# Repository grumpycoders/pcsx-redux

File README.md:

<a href='https://ko-fi.com/nicolasnoble' target='_blank'>Buy Me a Coffee at ko-fi.com</a>

|Platform|Build status|Download|
|--------|------------|--------|
|Windows x64 build||[Windows Intel 64-bits](https://distrib.app/pub/org/pcsx-redux/project/dev-win-x64)|
|Linux x64 build||[Linux Intel 64-bits (AppImage)](https://distrib.app/pub/org/pcsx-redux/project/dev-linux-x64)|
|Linux arm64 build||[Linux Arm 64-bits (AppImage)](https://distrib.app/pub/org/pcsx-redux/project/dev-linux-arm64)|
|macOS build||[macOS Arm](https://distrib.app/pub/org/pcsx-redux/project/dev-macos-arm)|
|Browser build||[Run in the browser (experimental)](https://tools.psx.dev/redux/)|

To discuss this emulator specifically, please join our Discord server:

To discuss PlayStation 1 development, hacking, and reverse engineering in general, please join the PSX.Dev Discord server:

# PCSX-Redux

## What?
The PCSX-Redux project is a collection of tools, research, hardware design, and libraries aiming at development and reverse engineering on the PlayStation 1. The core product itself, PCSX-Redux, is yet another fork of the Playstation emulator, PCSX. While the work here is very much in progress, the goal is roughly the following:

 - Bring the codebase to more up to date code standards.
 - Get rid of the plugin system and create a single monolithic codebase that handles all aspects of the playstation emulation.
 - Write everything on top of OpenGL3+/ImGui for portability and readability.
 - Improve the debugging experience.
 - Improve the rendering experience.

Please consult [the documentation pages](https://pcsx-redux.consoledev.net) for more information on the emulator itself.

The [tools](tools) directory contains a few tools that can be used to work with PlayStation 1 software. The [wiki](https://github.com/pcsx-redux/pcsx-redux/wiki) directory contains a few research information that are not directly related to the emulator itself. The [mips](src/mips) directory contains various pieces of code targeting the PlayStation 1, and importantly, the OpenBIOS project, which is a MIPS R3000A BIOS implementation that can be used to boot PlayStation 1 games without the need for a retail BIOS. And the [hardware](hardware) directory contains various hardware designs that can be used with the PlayStation 1.

## Where?
|Download page|
|--------|
|[Windows Intel 64-bits](https://distrib.app/pub/org/pcsx-redux/project/dev-win-x64)|
|[Windows Intel 64-bits CLI](https://distrib.app/pub/org/pcsx-redux/project/dev-win-cli-x64)|
|[Linux Intel 64-bits (AppImage)](https://distrib.app/pub/org/pcsx-redux/project/dev-linux-x64)|
|[Linux Arm 64-bits (AppImage)](https://distrib.app/pub/org/pcsx-redux/project/dev-linux-arm64)|
|[MacOS Arm](https://distrib.app/pub/org/pcsx-redux/project/dev-macos-arm)|
|[Browser (WebAssembly, experimental)](https://tools.psx.dev/redux/)|

All native builds are 64-bit only, and need a GPU and driver that can create at least an OpenGL 3.0 context. The emulator asks for a 3.3 core profile first and falls back to 3.0 if that fails.

The browser build is highly experimental and not really functional yet: expect missing features and breakage. It is redeployed from each push to main whose wasm build succeeds. It runs the CPU interpreter only and boots OpenBIOS, and it needs WebGL2 and SharedArrayBuffer. The first visit reloads the page once to enable SharedArrayBuffer.

The Linux AppImages are built on Ubuntu 24.04 and need a distribution at least that recent. On older ones, the Windows build runs under Wine 11: replace `pcsx-redux.exe`, the launcher that checks for the Visual C++ runtime, with `pcsx-redux.main` renamed to `pcsx-redux.exe`.

### Note:
The macOS version of PCSX-Redux is not currently signed with a developer certificate so you may see a security warning when opening the application.

If you see a dialog with the message:

> “PCSX-Redux” can’t be opened because Apple cannot check it for malicious software.

You can allow the application to run by doing either of the following. You only need to do this once for freshly downloaded copies of PCSX-Redux.

- Right-click the app and select Open. This signals an explicit decision on your part that you really want to open it, and adds a new "Open" button to the security warning dialog.

- Alternatively, go to macOS Settings > Privacy & Security. Scroll down to see a section that will let you allow the app.

## How?
The code is meant to be built using very modern compilers. Also it's still fairly experimental, and lots of things can break. If you still want to proceed, here are instructions to build it on Linux, MacOS and Windows. The code now comes in two big parts: the emulator itself, and [OpenBIOS](https://github.com/pcsx-redux/nugget/tree/main/openbios), which can be used as an alternative to the retail, copyright protected BIOS.

### Getting sources
The only location for the source is [on GitHub](https://github.com/pcsx-redux/pcsx-redux/).
Clone recursively, as the project uses submodules:
```
git clone --recursive https://github.com/pcsx-redux/pcsx-redux.git
```

### Windows
Install [Visual Studio 2022 Community Edition](https://visualstudio.microsoft.com/thank-you-downloading-visual-studio/?sku=Community&rel=16) using the `Desktop development with C++` workload. Open the file `vsprojects\pcsx-redux.sln`, select `pcsx-redux -> pcsx-redux`, right click, `Set as Startup Project`, and hit `F7` to build. The project follows the open-and-build paradigm with no extra step, so no specific dependency ought to be needed, as [NuGet](https://www.nuget.org/) will take care of downloading them automatically for you on the first build.

Note: If you get an error saying `hresult e_fail has been returned from a call to a com component`, you might need to delete the .suo file in vsproject/vs, restart Visual Studio and retry.

If you want to compile OpenBIOS or other PS1 software, you need to install a MIPS toolchain on Windows. You can do this by copy-pasting the following into a command prompt:

```powershell
powershell -c "& { iwr -UseBasicParsing https://bit.ly/mips-ps1 | iex }"
```

Then, open a new command prompt, and type the following:

```
mips install 16.2.0
```

To manually install this script, you can download it from [here](https://bit.ly/mips-ps1), and then install it with the following command:

```powershell
powershell -ExecutionPolicy Unrestricted -File mips.ps1 self-install C:\path\to\destination
```

You can leave the installation path blank to install the script in the Application Data folder.

Once the toolchain is installed, you can compile OpenBIOS using `make -C src/mips/openbios`.

### Linux
Run `./dockermake.sh appimage`. You need [docker](https://en.wikipedia.org/wiki/Docker_(software)) for this to work. This will create an [AppImage](https://appimage.org/) file, called `PCSX-Redux-HEAD-x86_64.AppImage` or `PCSX-Redux-HEAD-aarch64.AppImage` depending on your machine, which a self-hosted binary containing all of its required dependencies. Alternatively, if you do not want to use Docker, you can also simply install the dependencies listed below and run `make`.

#### GNU/Linux Dependencies

If you're only interested in compiling psx code, you can simply clone the pcsx-redux repo, then build the mips toolchain with [this script](https://github.com/pcsx-redux/pcsx-redux/blob/main/tools/linux-mips/spawn-compiler.sh), then follow the instructions in `/pcsx-redux/src/mips/psyq/README.md` to convert the PsyQ libraries. You might find them pre-compiled online.

 - Debian derivatives ( for full emulator compilation ):

```bash
sudo apt-get install -y build-essential git make pkg-config clang g++ libcapstone-dev libfreetype-dev libavcodec-dev libavformat-dev libavutil-dev libcurl4-openssl-dev libsdl3-dev libswresample-dev libuv1-dev zlib1g-dev
```

The mips toolchain isn't packaged by Debian or Ubuntu, so build it from source:

```bash
sudo apt-get install -y wget bzip2 xz-utils bison flex texinfo libgmp-dev libmpfr-dev libmpc-dev
sudo bash tools/linux-mips/spawn-compiler.sh
```

 - Arch derivatives :

The `pcsx-redux-git` package can be installed from the AUR using your AUR helper of choice (e.g., paru):

```bash
paru -S pcsx-redux-git
```

Alternatively, the following steps describe how to install dependencies and compile manually:

```bash
sudo pacman -S --needed capstone clang git make pkg-config ffmpeg libuv zlib sdl3 curl xorg-server-xvfb imagemagick
```
The mipsel environment can be installed from [AUR](https://wiki.archlinux.org/index.php/Aur) : [mipsel-none-elf-binutils](https://aur.archlinux.org/packages/mipsel-none-elf-binutils/) and [mipsel-none-elf-gcc](https://aur.archlinux.org/packages/mipsel-none-elf-gcc/) using your [AURhelper](https://wiki.archlinux.org/index.php/AUR_helpers) of choice:

```bash
trizen -S mipsel-none-elf-binutils mipsel-none-elf-gcc
```
You can then just enter the 'pcsx-redux' directory and compile without using docker with `make`.

Building OpenBIOS on Linux can be done with `./dockermake.sh -C src/mips/openbios`, or with `make -C src/mips/openbios` once you have a mipsel-none-elf toolchain. If you have a different mips compiler, you'll need to override some variables, such as `PREFIX` and `FORMAT`.

### MacOS
You need MacOS Catalina or later with the latest XCode to build, as well as a few [homebrew](https://brew.sh/) packages. Run the [brew installation script](https://github.com/pcsx-redux/pcsx-redux/blob/main/.github/scripts/install-brew-dependencies.sh) to get all the necessary dependencies. Simply run `make` to build.

Compiling OpenBIOS will require a mips compiler, which you can install from our [Homebrew tap](https://github.com/pcsx-redux/homebrew-mips):
```bash
brew install pcsx-redux/mips/mipsel-none-elf-gcc
```

Then, you can compile OpenBIOS using `make -C ./src/mips/openbios`.

## Who?
I used to contribute to the PCSX codebase. It is very likely that a sourceforge account of mine still has write access to the old cvs repository for PCSX. A long time ago, I contributed the telnet debugger, and the parallel port support. This means I am fairly familiar with this codebase, and I am also ashamed of the contributions I have done 15+ years ago, as one should.

Since the inception of this codebase, several people have contributed to it. Please refer to the [AUTHORS](AUTHORS) file for a (hopefully) exhaustive list.

## Why?
When Sony released the Playstation Classic recently, I came to realize two things: first, the state of the Playstation emulation isn't that great, and second, the only half-decent debugging tool still available for this console is that old telnet debugger I wrote eons ago, while other emulators out there for other consoles gained a lot of debugging superpowers. I think it was time for the Playstation emulation to get to better standards with regards to debuggability. I also felt I had a responsability to cleaning up some of the horrors I've introduced myself in the codebase long ago, and that made me cry a little looking at them. Hopefully, I got better at programming. Hopefully.

## Status?
The codebase still requires a lot of cleanup, and while the product is usable in its current state and lots can be achieved with it, there is still ways to go for reaching the first stable release. If you want to help with localization, you can find the translation project [on transifex](https://explore.transifex.com/grumpycoders/pcsx-redux/).

### What works?
- Dynamic Recompiler (x86-64, experimental arm64 support)
- interpreted CPU
- software GPU
- OpenGL GPU (highly experimental, still in active development)
- support for visual enhancements:
  - Linear and nearest neighbour filtering (Software and OpenGL renderer)
  - Rendering in true colour (Results in better colours, OpenGL renderer only)
  - Antialiasing (Implemented via MSAA, OpenGL renderer only)
  - Ability to optionally render polygons as wireframe or as vertices (Helps with debugging, OpenGL renderer only)
  - Hopefully more to come in the feature, such as upscaling, integer scaling, PGXP, and more
- VRAM viewer and debugger
- fully featured MIPS debugger
- memory cards
- memory card manager
- XBox controller support
- digital and analog controller emulation, Playstation Mouse emulation
- Lua scripting
- SPU debugger
- in-app shader editor and built-in crt-lottes shader
- customizable UI
- save states

### What still requires some work?
- fix remaining OpenGL renderer bugs (No mask bit emulation, missing commands, etc) and add more graphics enhancements
- proper SPU multithreaded code
- better customization
- more generic dynarec
- hook more emulator functions to Lua
- see [TODO](TODO.md) for more

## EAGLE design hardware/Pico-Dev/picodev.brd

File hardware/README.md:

# Hardware

This directory contains various hardware mods and addons for the PlayStation 1. The PCBs have been designed using Eagle, and pre-rendered gerber files are provided. When applicable, [jlcpcb](https://jlcpcb.com) build files are provided (BoM and assembly CSV files).

Some of these designs have been thoroughly documented [in the wiki](https://github.com/grumpycoders/pcsx-redux/wiki).

* [MC-Breakout](MC-Breakout) - A breakout board for the PlayStation 1's memory card slot. This board is made to fit directly into the slot without a case, and provides a simple header to connect to the memory card slot's signals.

* [PIO-Breakout](PIO-Breakout) - A breakout board for the PlayStation 1's parallel I/O port. This board is designed to function as a pass-through, which can then be used to sniff the parallel I/O port's signals when connecting another flash cart to it.

* [PIO-Dev](PIO-Dev) - A development board for the PlayStation 1's parallel I/O port. The board has [extensive documentation](https://github.com/grumpycoders/pcsx-redux/wiki/PIODev-Board) on the wiki.

* [PIO-Dev-Lite](PIO-Dev-Lite) - A smaller version of the PIO-Dev board, with a few less features. It is fitted with a writable flash, an FT232H chip for fast communication, and header pins to connect a [CH376 module](https://www.google.com/search?q=ch376+module). The CH376 module can be used with [Skitchin's project](https://github.com/johnbaumann/psx-wch376s) to access USB mass storage.

* [Pico-Dev](Pico-Dev) - A development board for the PlayStation 1 based on the Raspberry Pi Pico. It is extremely simple to manufacture, as its BoM is exactly one [RP2040-Zero](https://www.waveshare.com/rp2040-zero.htm), one PIO port, and one Schottky diode. The firmware for it is avaiable at [https://github.com/johnbaumann/PicoDev](https://github.com/johnbaumann/PicoDev).

* [PowerReplayUSB](PowerReplayUSB) - An easy to build mod for the popular and readily available [Power Replay Flash Cart](https://www.aliexpress.com/w/wholesale-ps1-power-replay.html) which adds USB support to it. The USB support is provided by the [FT232H](https://ftdichip.com/products/ft232hq/) chip, and [unirom](https://unirom.github.io/) has support for it. There is a [USB-C alternative](PowerReplayUSBC) available as well.

The projects featuring FT232H chips can be used for ultra fast communication between the PlayStation 1 and a computer. [Tools made by danhans42](https://github.com/danhans42/psx232h) can be used for this.

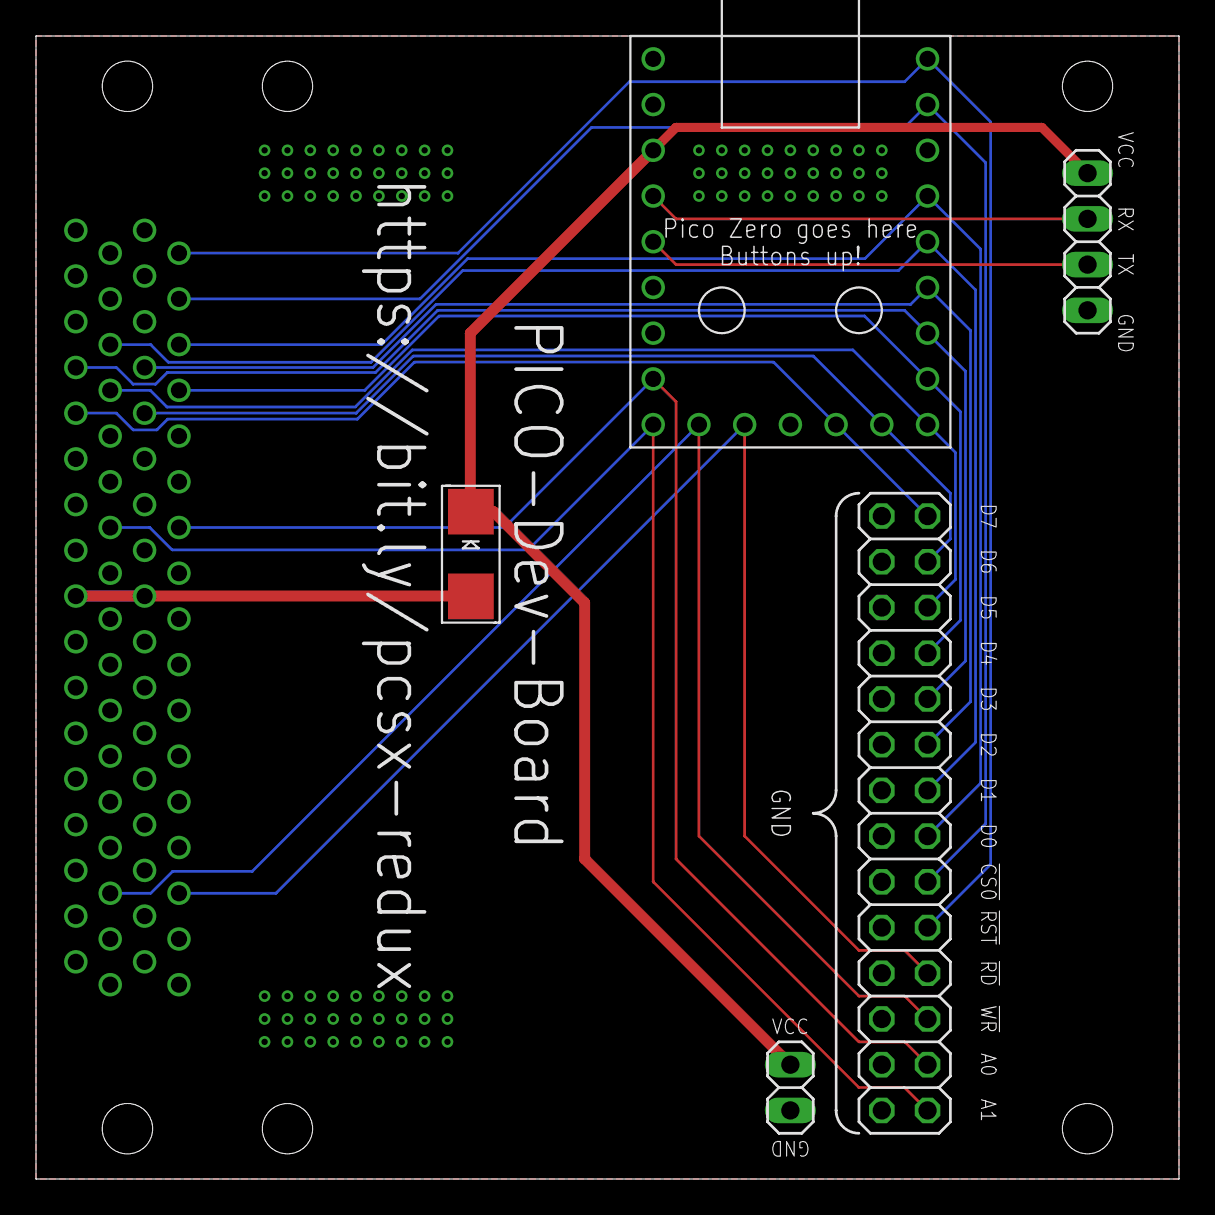
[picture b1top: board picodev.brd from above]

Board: 2 copper layers, 63.5 x 63.5 mm, 6 parts (1 on the bottom side), 19 nets.

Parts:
D: SCHOTTKYSMA; SMADIODE
DEBUG: 2X14
PIO: PIOCONNPIOCONN-S; PIOCONN
PWR: 1X02
U$1: PICO-ZERO
UART: 1X04

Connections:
!CS0: DEBUG.18, PIO.4, U$1.2
!RD: DEBUG.22, PIO.30, U$1.13
!RESET: DEBUG.20, PIO.2, U$1.1
!WR: DEBUG.24, PIO.64, U$1.14
A0: DEBUG.26, PIO.14, U$1.16
A1: DEBUG.28, PIO.48, U$1.15
D0: DEBUG.16, PIO.6, U$1.4
D1: DEBUG.14, PIO.40, U$1.5
D2: DEBUG.12, PIO.7, U$1.6
D3: DEBUG.10, PIO.41, U$1.7
D4: DEBUG.8, PIO.8, U$1.8
D5: DEBUG.6, PIO.42, U$1.9
D6: DEBUG.4, PIO.9, U$1.10
D7: DEBUG.2, PIO.43, U$1.11
GND: DEBUG.1, DEBUG.3, DEBUG.5, DEBUG.7, DEBUG.9, DEBUG.11, DEBUG.13, DEBUG.15, DEBUG.17, DEBUG.19, DEBUG.21, DEBUG.23, DEBUG.25, DEBUG.27, PIO.1, PIO.16, PIO.19, PIO.34, PIO.35, PIO.50, PIO.53, PIO.68, PWR.1, U$1.22, UART.1
PIOVCC33: D.A, PIO.17, PIO.51
RX: U$1.20, UART.3
TX: U$1.19, UART.2
VCC33: D.C, PWR.2, U$1.21, UART.4

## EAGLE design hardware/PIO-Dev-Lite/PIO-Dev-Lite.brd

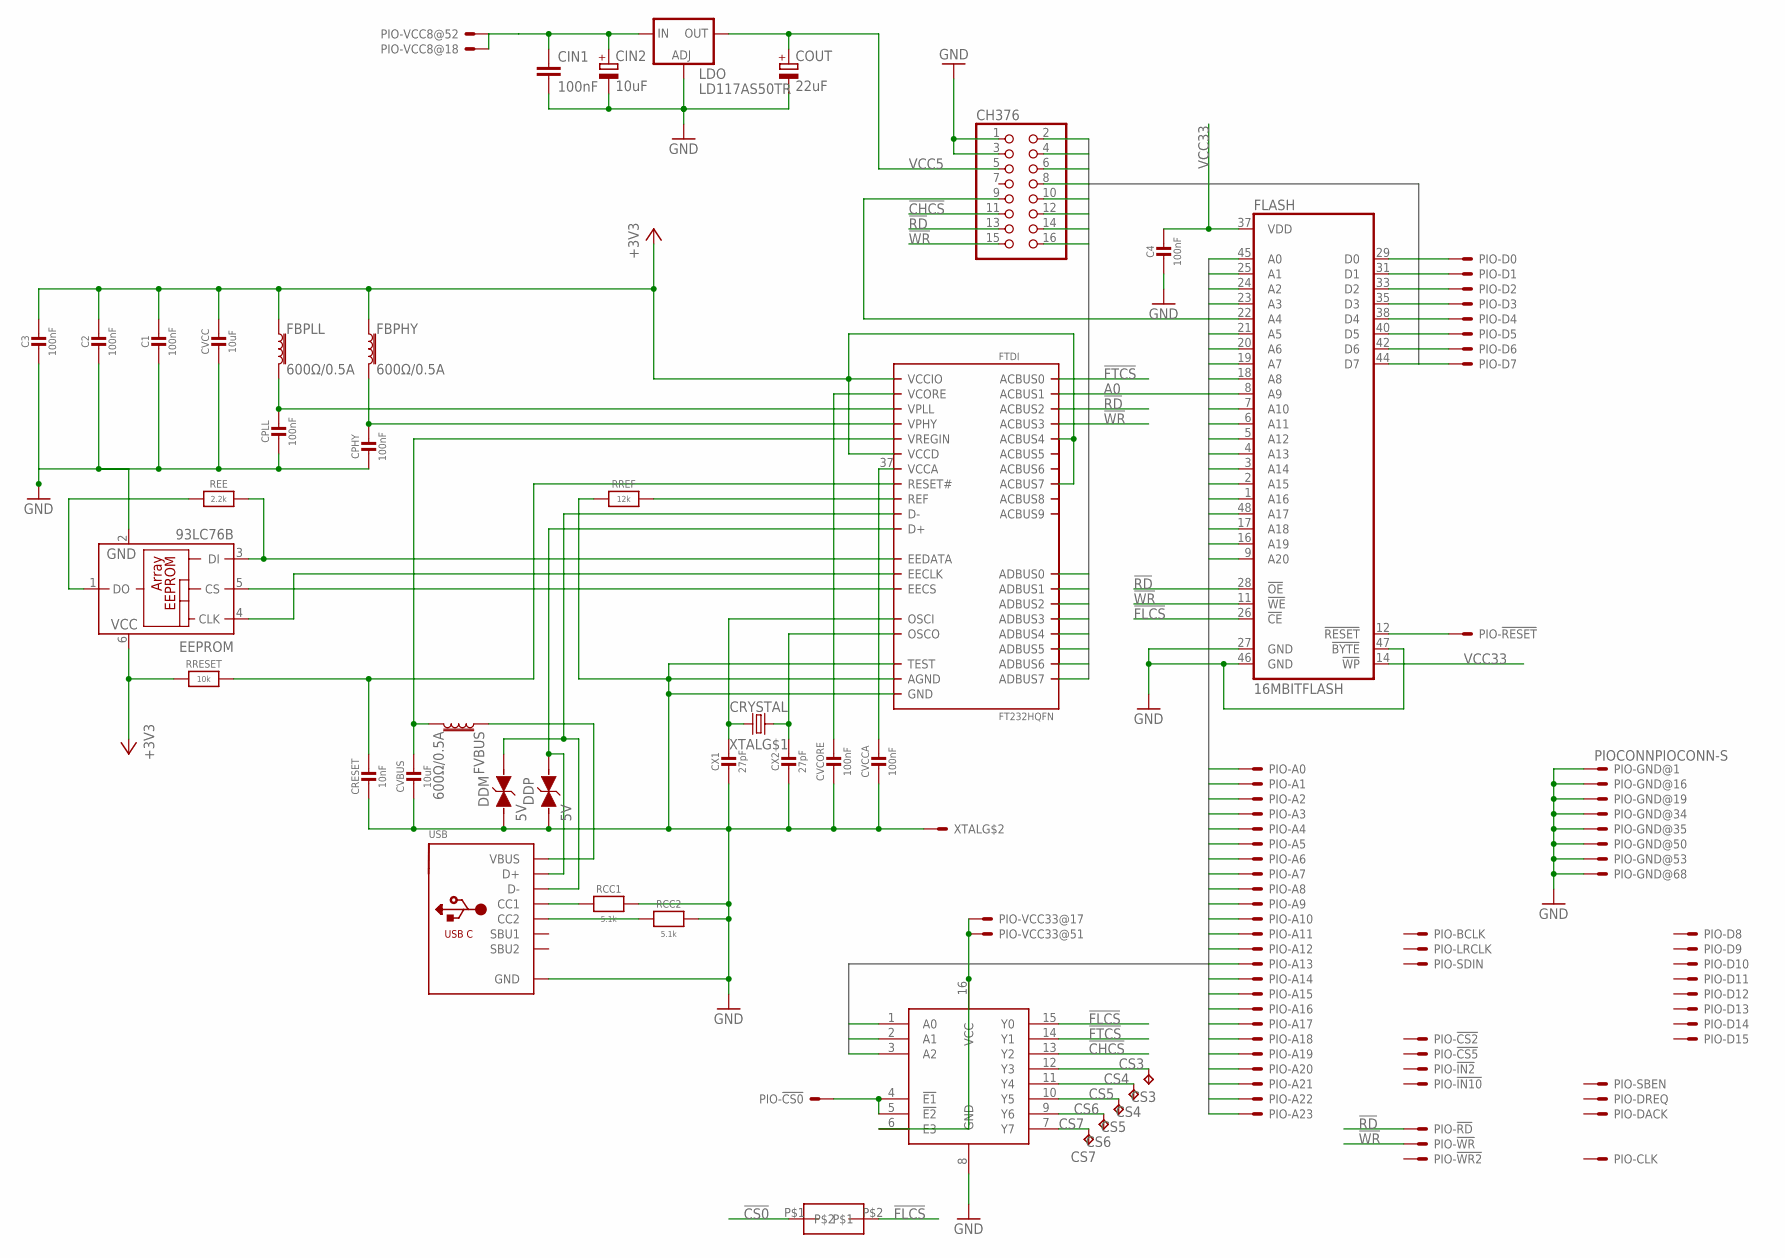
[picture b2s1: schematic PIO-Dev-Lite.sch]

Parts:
C1, C2, C3, C4: 100nF; 0603
CH376: PINHD-2X8; 2X08
CIN1: 100nF; C0603K
CIN2: 10uF; A/3216-18W
COUT: 22uF; A/3216-18W
CPHY: 100nF; 0603
CPLL: 100nF; 0603
CRESET: 10nF; 0603
CS3, CS4, CS5, CS6, CS7: TP
CVBUS: 10uF; 1206
CVCC: 10uF; 1206
CVCCA: 100nF; 0603
CVCORE: 100nF; 0603
CX1, CX2: 27pF; 0402
DDM: 5V; WE-VE_0603
DDP: 5V; WE-VE_0603
DECODER: 74HC138; TSSOP16
EEPROM: 93LC76B; SOT23-6
FBPHY: 600Ω/0.5A; 0603
FBPLL: 600Ω/0.5A; 0603
FLASH: 16MBITFLASH; TSOP48
FTDI: FT232HQFN; QFN48_8MM
FVBUS: 600Ω/0.5A; 0603
LDO: LD117AS50TR; SOT223
NOUSB: SMD-JUMPER
PIO: PIOCONNPIOCONN-S; PIOCONN
RCC1, RCC2: 5.1k; 0402
REE: 2.2k; 0603
RREF: 12k; 0603
RRESET: 10k; 0603
USB: USB-C
XTAL: CRYSTAL; SMD3225-4P

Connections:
!CHCS: CH376.11, DECODER.13 (Y2)
!CS0: DECODER.4 (!E1), DECODER.5 (!E2), NOUSB.P$1, PIO.4
!FLCS: DECODER.15 (Y0), FLASH.26 (!CE), NOUSB.P$2
!FTCS: DECODER.14 (Y1), FTDI.21 (ACBUS0)
!RD: CH376.13, FLASH.28 (!OE), FTDI.26 (ACBUS2), PIO.30
!RESET: FLASH.12 (!RESET), PIO.2
!RESET_FT: CRESET.1, FTDI.34 (RESET#), RRESET.2
!WR: CH376.15, FLASH.11 (!WE), FTDI.27 (ACBUS3), PIO.64
+3V3: C1.1, C2.1, C3.1, CVCC.1, EEPROM.6 (VCC), FBPHY.1, FBPLL.1, FTDI.12 (VCCIO), FTDI.24 (VCCIO), FTDI.28 (ACBUS4), FTDI.31 (ACBUS7), FTDI.39 (VCCD), FTDI.46 (VCCIO), RRESET.1
A0: CH376.9, FLASH.45 (A0), FTDI.25 (ACBUS1), PIO.14
A1: FLASH.25 (A1), PIO.48
A2: FLASH.24 (A2), PIO.15
A3: FLASH.23 (A3), PIO.49
A4: FLASH.22 (A4), PIO.20
A5: FLASH.21 (A5), PIO.54
A6: FLASH.20 (A6), PIO.21
A7: FLASH.19 (A7), PIO.55
A8: FLASH.18 (A8), PIO.22
A9: FLASH.8 (A9), PIO.56
A10: FLASH.7 (A10), PIO.23
A11: FLASH.6 (A11), PIO.57
A12: FLASH.5 (A12), PIO.24
A13: FLASH.4 (A13), PIO.58
A14: FLASH.3 (A14), PIO.25
A15: FLASH.2 (A15), PIO.59
A16: FLASH.1 (A16), PIO.26
A17: FLASH.48 (A17), PIO.60
A18: FLASH.17 (A18), PIO.27
A19: FLASH.16 (A19), PIO.61
A20: FLASH.9 (A20), PIO.28
A21: DECODER.1 (A0), PIO.62
A22: DECODER.2 (A1), PIO.29
A23: DECODER.3 (A2), PIO.63
CC1: RCC1.1, USB.A5 (CC1)
CC2: RCC2.1, USB.B5 (CC2)
CS3: CS3.P$1, DECODER.12 (Y3)
CS4: CS4.P$1, DECODER.11 (Y4)
CS5: CS5.P$1, DECODER.10 (Y5)
CS6: CS6.P$1, DECODER.9 (Y6)
CS7: CS7.P$1, DECODER.7 (Y7)
D0: CH376.2, FLASH.29 (D0), FTDI.13 (ADBUS0), PIO.6
D1: CH376.4, FLASH.31 (D1), FTDI.14 (ADBUS1), PIO.40
D2: CH376.6, FLASH.33 (D2), FTDI.15 (ADBUS2), PIO.7
D3: CH376.8, FLASH.35 (D3), FTDI.16 (ADBUS3), PIO.41
D4: CH376.10, FLASH.38 (D4), FTDI.17 (ADBUS4), PIO.8
D5: CH376.12, FLASH.40 (D5), FTDI.18 (ADBUS5), PIO.42
D6: CH376.14, FLASH.42 (D6), FTDI.19 (ADBUS6), PIO.9
D7: CH376.16, FLASH.44 (D7), FTDI.20 (ADBUS7), PIO.43
DM: DDM.1, FTDI.6 (D-), USB.A7 (D-), USB.B7 (D-)
DP: DDP.1, FTDI.7 (D+), USB.A6 (D+), USB.B6 (D+)
EECLK: EEPROM.4 (CLK), FTDI.44 (EECLK)
EECS: EEPROM.5 (CS), FTDI.45 (EECS)
EEDATA: EEPROM.3 (DI), FTDI.43 (EEDATA), REE.2
EEDO: EEPROM.1 (DO), REE.1
GND: C1.2, C2.2, C3.2, C4.2, CH376.1, CH376.3, CIN1.2, CIN2.-, COUT.-, CPHY.2, CPLL.2, CRESET.2, CVBUS.2, CVCC.2, CVCCA.2, CVCORE.2, CX1.2, CX2.2, DDM.2, DDP.2, DECODER.8 (GND), EEPROM.2 (GND), FLASH.27 (GND), FLASH.46 (GND), FLASH.47 (!BYTE), FTDI.4 (AGND), FTDI.9 (AGND), FTDI.10 (GND), FTDI.11 (GND), FTDI.22 (GND), FTDI.23 (GND), FTDI.35 (GND), FTDI.36 (GND), FTDI.41 (AGND), FTDI.42 (TEST), FTDI.47 (GND), FTDI.48 (GND), FTDI.THERMAL (GND), LDO.1 (ADJ), PIO.1, PIO.16, PIO.19, PIO.34, PIO.35, PIO.50, PIO.53, PIO.68, RCC1.2, RCC2.2, RREF.1, USB.A1B12 (GND), USB.B1A12 (GND), USB.M1 (GND), USB.M2 (GND), USB.M3 (GND), USB.M4 (GND), XTAL.P$2 (S), XTAL.P$4 (S)
REF: FTDI.5 (REF), RREF.2
VBUS: FVBUS.1, USB.A4B9 (VBUS), USB.B4A9 (VBUS)
VCC5: CH376.5, COUT.+, LDO.4 (OUT)
VCC8: CIN1.1, CIN2.+, LDO.3 (IN), PIO.18, PIO.52
VCC33: C4.1, DECODER.6 (E3), DECODER.16 (VCC), FLASH.14 (!WP), FLASH.37 (VDD), PIO.17, PIO.51
VCCA: CVCCA.1, FTDI.37 (VCCA)
VCORE: CVCORE.1, FTDI.38 (VCORE)
VPHY: CPHY.1, FBPHY.2, FTDI.3 (VPHY)
VPLL: CPLL.1, FBPLL.2, FTDI.8 (VPLL)
VREGIN: CVBUS.1, FTDI.40 (VREGIN), FVBUS.2
XI: CX1.1, FTDI.1 (OSCI), XTAL.P$1 (X1)
XO: CX2.1, FTDI.2 (OSCO), XTAL.P$3 (X2)

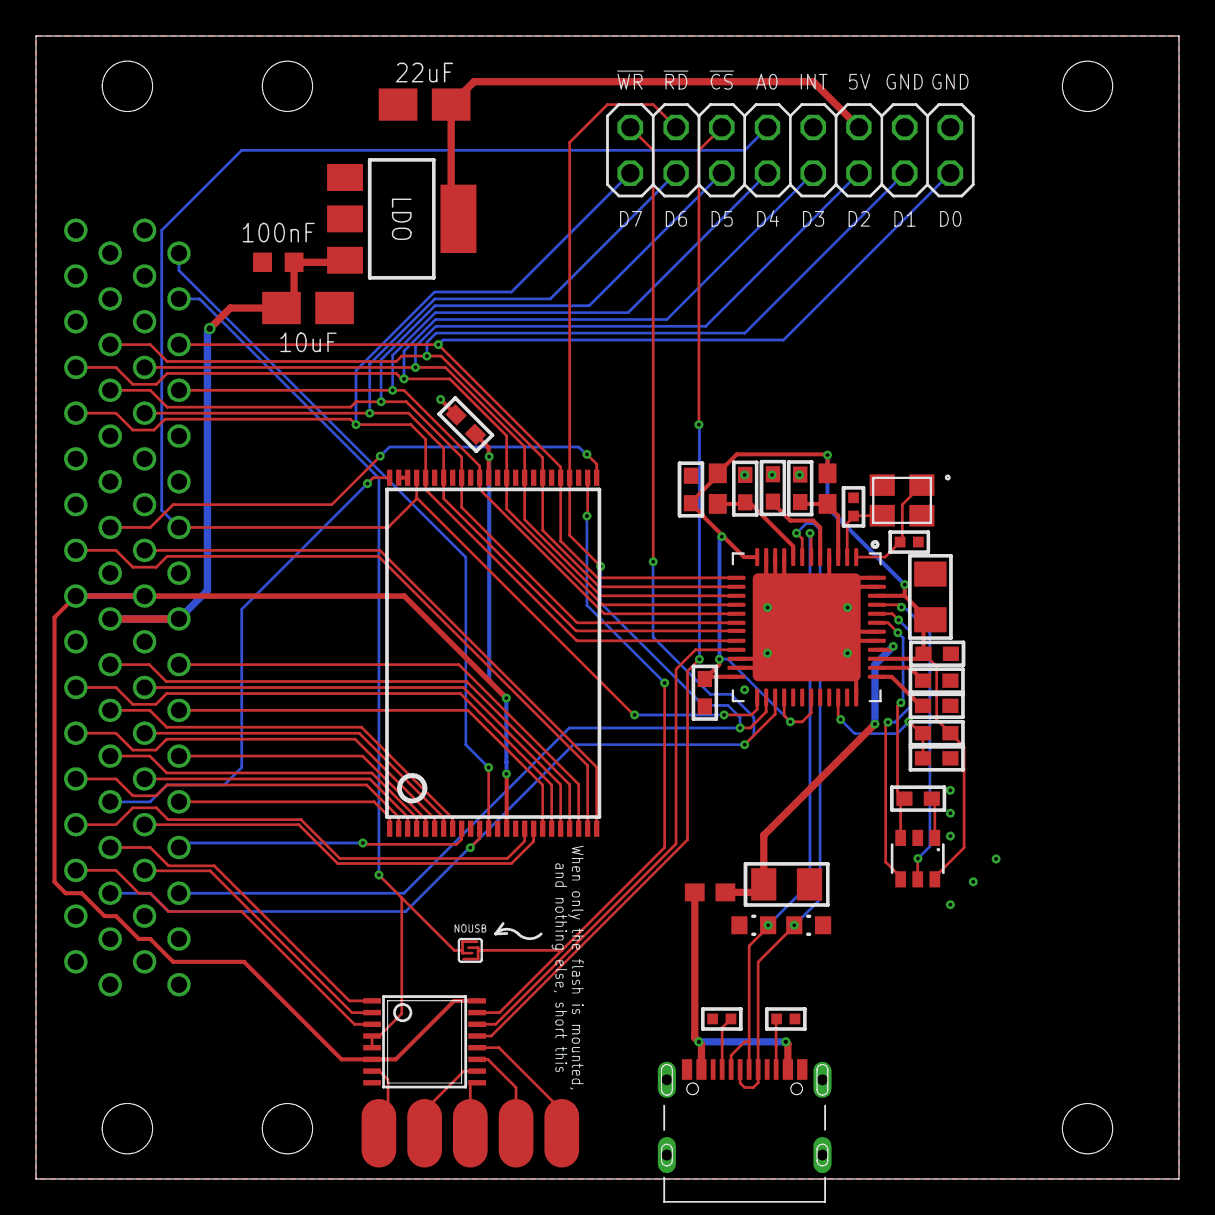
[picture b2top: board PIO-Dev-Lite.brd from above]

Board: 2 copper layers, 63.5 x 63.5 mm, 41 parts (1 on the bottom side), 67 nets.

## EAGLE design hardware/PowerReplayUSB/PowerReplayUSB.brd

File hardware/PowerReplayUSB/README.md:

# PowerReplayUSB

An FT232H mod for the Power Replay cart. The board solders onto the castellations where the cart's missing comms buffer would go. [PowerReplayUSBC](../PowerReplayUSBC) is the same board with a USB-C connector.

## Ordering

The `GerberFiles` directory and the two CSV files are ready for JLCPCB's assembly service.

- `GATES` is a 74AHC02PW (C55190887). The SN74AHC02PWR it replaces is close to out of stock at LCSC. The 7402 is powered from the cart's 5V rail, so it needs a family specified for a 5V supply (AHC, HC). A 74LVC02 is not: its inputs tolerate 5.5V but its supply is specified up to 3.6V.
- The schematic says 93LC76B for the EEPROM. The BOM's C190271 is a 93LC56B, the part FTDI's datasheet names.
- The FT232HQ (C82158) is often low in stock. Check it before ordering.

## Registers

The FT232H only answers when A2=0 and A4=0, anywhere in 0x1f060000-0x1f07ffff, and only 0x1f060008 decodes writes. Use these addresses:

- data: `0x1f060008`
- status: `0x1f060009`, bit 0 set when a byte can be read, bit 1 set when a byte can be written. Bits 4-7 follow the next byte in the receive FIFO, so mask the status to bits 0 and 1.

The stock EXP1 settings work. A read delay of 0 does not.

The FT232H is powered from the USB port only, so the console side reads an undriven bus when no computer is plugged in.

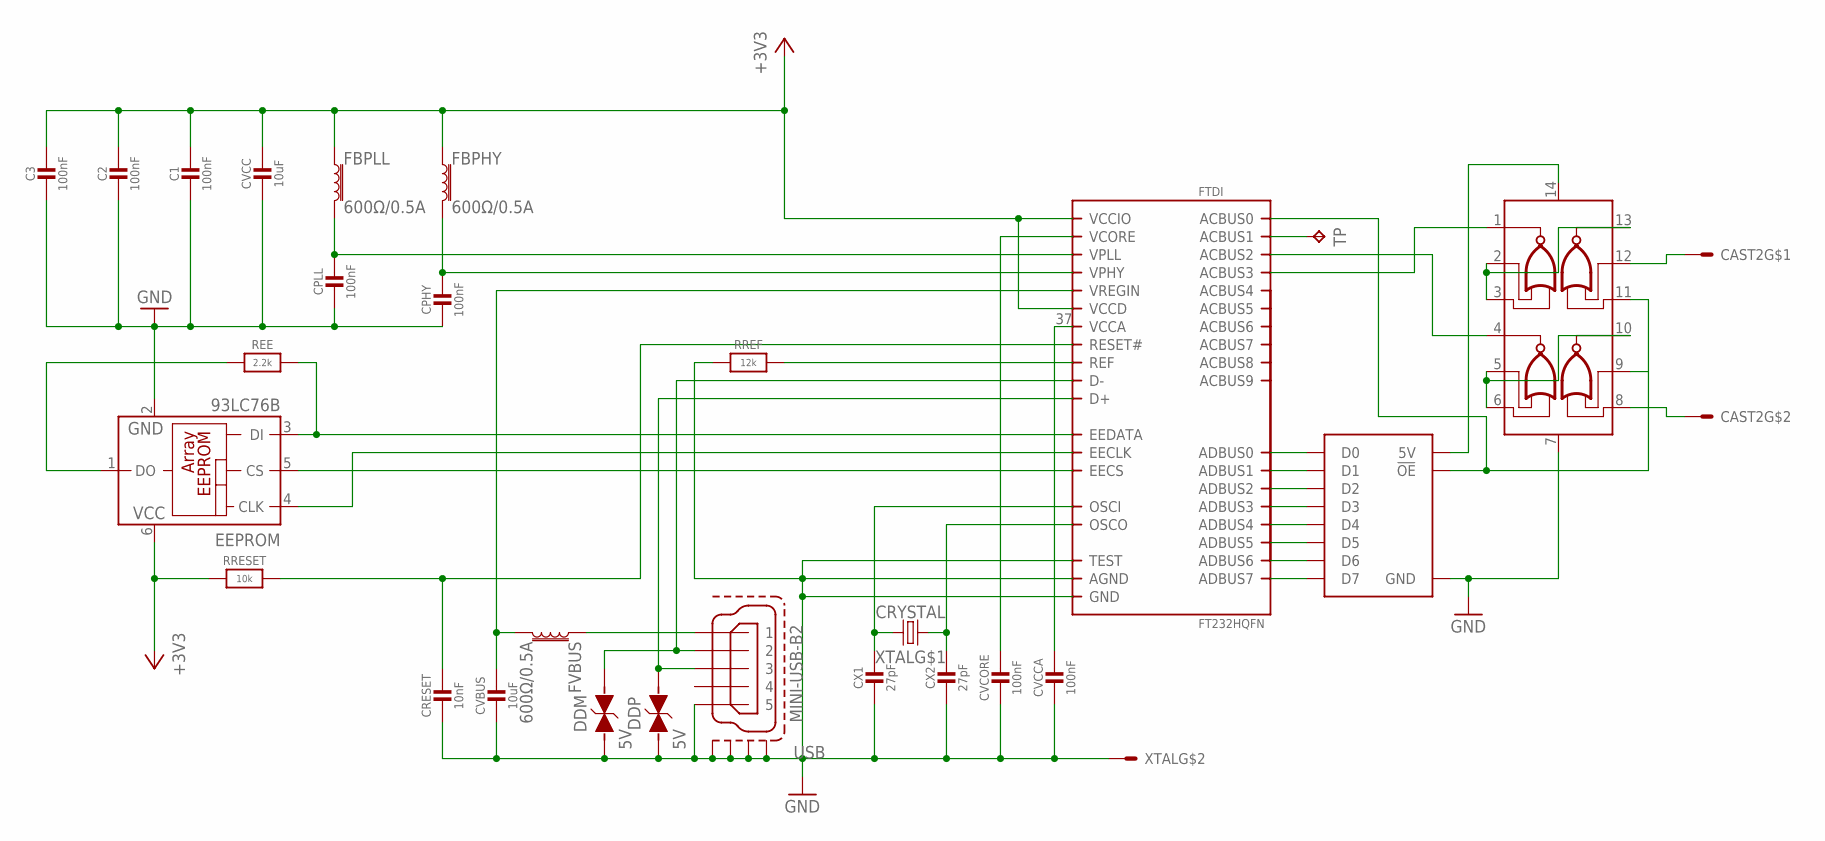
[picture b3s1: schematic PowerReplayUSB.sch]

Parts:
C1, C2, C3: 100nF; 0603
CAST1: BUFFER-CASTELLATION
CAST2: PLA-CASTELLATION
CPHY: 100nF; 0603
CPLL: 100nF; 0603
CRESET: 10nF; 0603
CVBUS: 10uF; 1206
CVCC: 10uF; 1206
CVCCA: 100nF; 0603
CVCORE: 100nF; 0603
CX1, CX2: 27pF; 0402
DDM: 5V; WE-VE_0603
DDP: 5V; WE-VE_0603
EEPROM: 93LC76B; SOT23-6
FBPHY: 600Ω/0.5A; 0603
FBPLL: 600Ω/0.5A; 0603
FTDI: FT232HQFN; QFN48_8MM
FVBUS: 600Ω/0.5A; 0603
GATES: 7402TSSOP14; TSSOP14-RU
REE: 2.2k; 0603
RREF: 12k; 0603
RRESET: 10k; 0603
TP: TP
USB: MINI-USB-B2; MINI-USB-B-2
XTAL: CRYSTAL; SMD3225-4P

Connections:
5V: CAST1.P$11 (5V), GATES.14
!RESET_FT: CRESET.1, FTDI.34 (RESET#), RRESET.2
+3V3: C1.1, C2.1, C3.1, CVCC.1, EEPROM.6 (VCC), FBPHY.1, FBPLL.1, FTDI.12 (VCCIO), FTDI.24 (VCCIO), FTDI.39 (VCCD), FTDI.46 (VCCIO), RRESET.1
A0: FTDI.25 (ACBUS1), TP.P$1
D0: CAST1.P$1 (D0), FTDI.13 (ADBUS0)
D1: CAST1.P$2 (D1), FTDI.14 (ADBUS1)
D2: CAST1.P$3 (D2), FTDI.15 (ADBUS2)
D3: CAST1.P$4 (D3), FTDI.16 (ADBUS3)
D4: CAST1.P$5 (D4), FTDI.17 (ADBUS4)
D5: CAST1.P$6 (D5), FTDI.18 (ADBUS5)
D6: CAST1.P$7 (D6), FTDI.19 (ADBUS6)
D7: CAST1.P$8 (D7), FTDI.20 (ADBUS7)
DM: DDM.1, FTDI.6 (D-), USB.P$2 (2)
DP: DDP.1, FTDI.7 (D+), USB.P$3 (3)
EECLK: EEPROM.4 (CLK), FTDI.44 (EECLK)
EECS: EEPROM.5 (CS), FTDI.45 (EECS)
EEDATA: EEPROM.3 (DI), FTDI.43 (EEDATA), REE.2
EEDO: EEPROM.1 (DO), REE.1
GND: C1.2, C2.2, C3.2, CAST1.P$9 (GND), CPHY.2, CPLL.2, CRESET.2, CVBUS.2, CVCC.2, CVCCA.2, CVCORE.2, CX1.2, CX2.2, DDM.2, DDP.2, EEPROM.2 (GND), FTDI.4 (AGND), FTDI.9 (AGND), FTDI.10 (GND), FTDI.11 (GND), FTDI.22 (GND), FTDI.23 (GND), FTDI.35 (GND), FTDI.36 (GND), FTDI.41 (AGND), FTDI.42 (TEST), FTDI.47 (GND), FTDI.48 (GND), FTDI.THERMAL (GND), GATES.7, RREF.1, USB.P$5 (5), USB.P$6 (S1), USB.P$7 (S2), USB.P$8 (S3), USB.P$9 (S4), XTAL.P$2 (S), XTAL.P$4 (S)
OE: CAST1.P$10 (!OE), FTDI.21 (ACBUS0), GATES.9, GATES.11
RD: CAST2.P$2, GATES.8
RD+CS: FTDI.26 (ACBUS2), GATES.4
REF: FTDI.5 (REF), RREF.2
RRD: GATES.5, GATES.6, GATES.10
RWR: GATES.2, GATES.3, GATES.13
VBUS: FVBUS.1, USB.P$1 (1)
VCCA: CVCCA.1, FTDI.37 (VCCA)
VCORE: CVCORE.1, FTDI.38 (VCORE)
VPHY: CPHY.1, FBPHY.2, FTDI.3 (VPHY)
VPLL: CPLL.1, FBPLL.2, FTDI.8 (VPLL)
VREGIN: CVBUS.1, FTDI.40 (VREGIN), FVBUS.2
WR: CAST2.P$1, GATES.12
WR+CS: FTDI.27 (ACBUS3), GATES.1
XI: CX1.1, FTDI.1 (OSCI), XTAL.P$1 (X1)
XO: CX2.1, FTDI.2 (OSCO), XTAL.P$3 (X2)

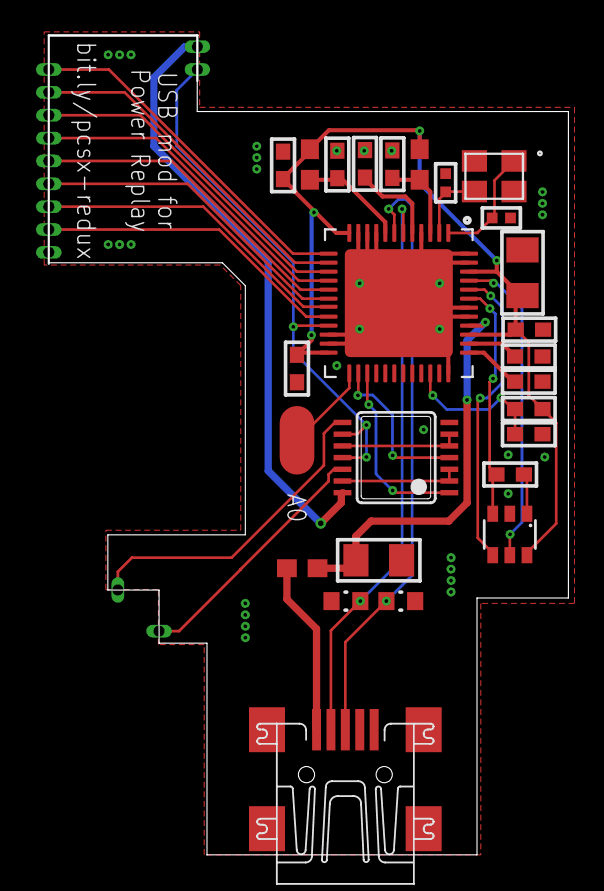
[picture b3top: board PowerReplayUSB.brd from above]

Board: 2 copper layers, 28.9 x 45.5 mm, 28 parts (0 on the bottom side), 35 nets.

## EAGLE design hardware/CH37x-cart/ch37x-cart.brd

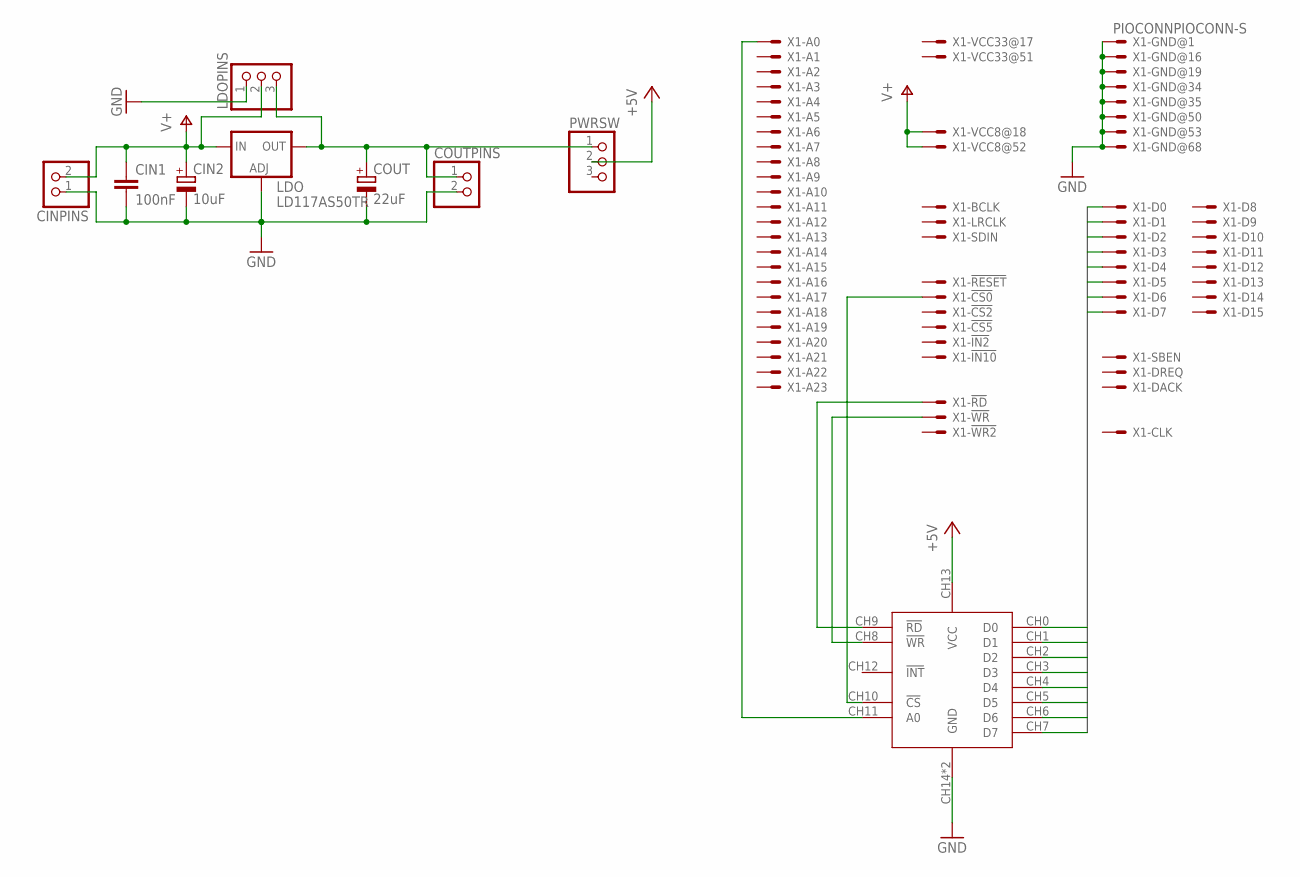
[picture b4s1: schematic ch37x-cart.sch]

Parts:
CH37XBOARD: CH375B-BOARD
CIN1: 100nF; C0603K
CIN2: 10uF; A/3216-18W
CINPINS: PINHD-1X2; 1X02
COUT: 22uF; A/3216-18W
COUTPINS: PINHD-1X2; 1X02
LDO: LD117AS50TR; SOT223
LDOPINS: PINHD-1X3; 1X03
PWRSW: PINHD-1X3; 1X03
X1: PIOCONNPIOCONN-S; PIOCONN

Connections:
5VALWAYS: COUT.+, COUTPINS.1, LDO.4 (OUT), LDOPINS.3, PWRSW.1
!CS0: CH37XBOARD.CH10 (!CS), X1.4
!RD: CH37XBOARD.CH9 (!RD), X1.30
!WR: CH37XBOARD.CH8 (!WR), X1.64
+5V: CH37XBOARD.CH13 (VCC), PWRSW.2
A0: CH37XBOARD.CH11 (A0), X1.14
D0: CH37XBOARD.CH0 (D0), X1.6
D1: CH37XBOARD.CH1 (D1), X1.40
D2: CH37XBOARD.CH2 (D2), X1.7
D3: CH37XBOARD.CH3 (D3), X1.41
D4: CH37XBOARD.CH4 (D4), X1.8
D5: CH37XBOARD.CH5 (D5), X1.42
D6: CH37XBOARD.CH6 (D6), X1.9
D7: CH37XBOARD.CH7 (D7), X1.43
GND: CH37XBOARD.CH14 (GND), CH37XBOARD.CH15 (GND), CIN1.2, CIN2.-, CINPINS.1, COUT.-, COUTPINS.2, LDO.1 (ADJ), LDOPINS.1, X1.1, X1.16, X1.19, X1.34, X1.35, X1.50, X1.53, X1.68
V+: CIN1.1, CIN2.+, CINPINS.2, LDO.3 (IN), LDOPINS.2, X1.18, X1.52

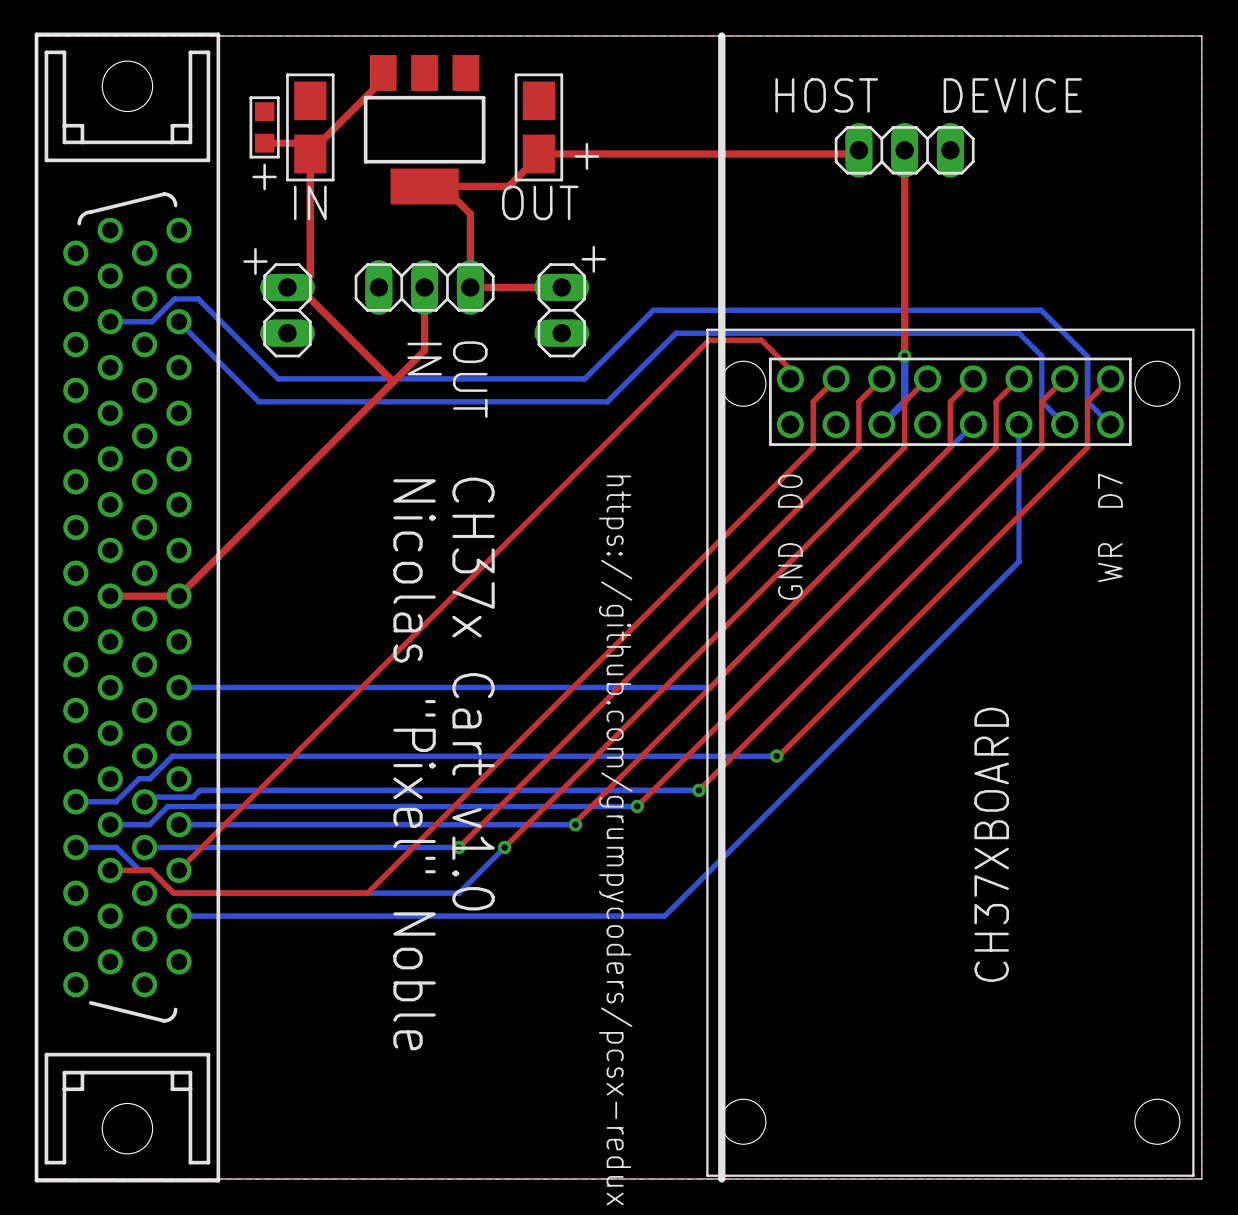
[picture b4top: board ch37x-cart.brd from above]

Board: 2 copper layers, 64.8 x 63.5 mm, 10 parts (0 on the bottom side), 16 nets.

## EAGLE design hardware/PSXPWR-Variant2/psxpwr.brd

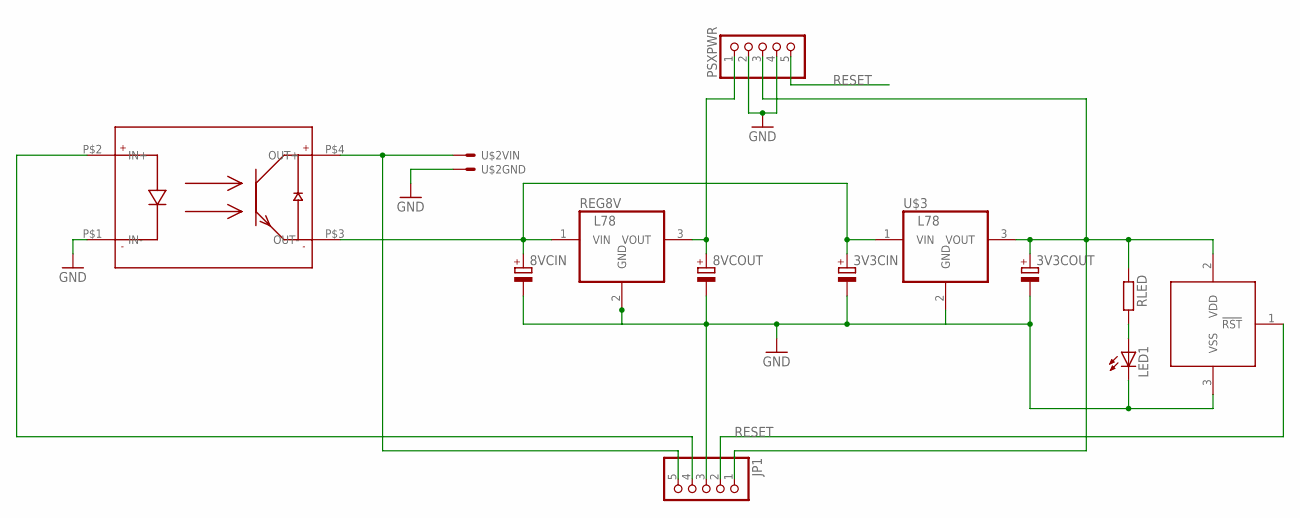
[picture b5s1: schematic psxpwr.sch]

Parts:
3V3CIN, 3V3COUT, 8VCIN, 8VCOUT: CPOL-EUE2.5-6; E2,5-6
JP1: PINHD-1X5; 1X05
LED1: LED3MM
PSXPWR: PINHD-1X5; 1X05
REG8V: L78; TO-220-HEATSINK
RESET: MCP100V3; TO92-EBC-OVAL
RLED: R-EU_0207/2V; 0207/2V
U$1: KF060XD
U$2: PWR
U$3: L78; TO-220-HEATSINK

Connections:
3V3: 3V3COUT.+, JP1.1, PSXPWR.3, RESET.2 (VDD), RLED.1, U$3.3 (VOUT)
8V: 8VCOUT.+, PSXPWR.1, REG8V.3 (VOUT)
12V: 3V3CIN.+, 8VCIN.+, REG8V.1 (VIN), U$1.P$3 (OUT-), U$3.1 (VIN)
GND: 3V3CIN.-, 3V3COUT.-, 8VCIN.-, 8VCOUT.-, JP1.3, LED1.K (C), PSXPWR.2, PSXPWR.4, REG8V.2 (GND), RESET.3 (VSS), U$1.P$1 (IN-), U$2.P$1, U$3.2 (GND)
LED: LED1.A, RLED.2
PON: JP1.4, U$1.P$2 (IN+)
RESET: JP1.2, PSXPWR.5, RESET.1 (!RST)
VIN: JP1.5, U$1.P$4 (OUT+), U$2.P$2

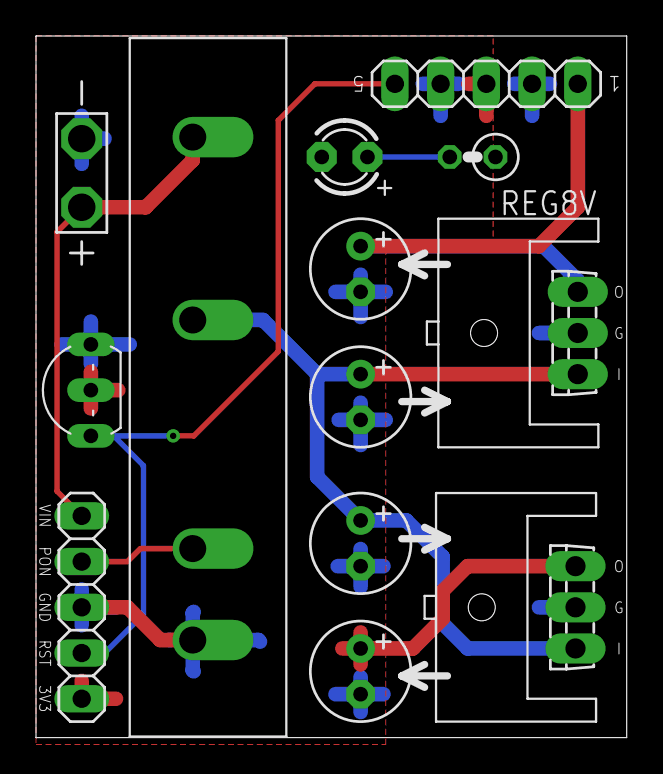
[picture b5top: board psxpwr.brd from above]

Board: 2 copper layers, 32.8 x 39.0 mm, 13 parts (0 on the bottom side), 8 nets.

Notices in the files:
parts and their libraries:
Wurth_EMC Components_WE-VE: Copyright: Würth Elektronik
SparkFun-Coils: Licensing: Creative Commons ShareAlike 4.0 International - https://creativecommons.org/licenses/by-sa/4.0
